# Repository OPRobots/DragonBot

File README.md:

# DragonBot
Robot siguelineas con succión centrifuga y STM32F1

## Hardware
- STM32F1 "BluePill"
- Driver de motores TB6612FNG
- 2x Motores Pololu N20 HP @3000rpm
- 1x Motor Brushless Rotorx
- LiPo 2S ~250 mAh
- 12x Sensores QRE1113
- 12x Potenciometros para regular la ganancia de los sensores
- Ruedas Scaleauto Procomp 1
- Chasis de PCB autosoportado con soportes de motores, ventilador y parachoques impresos en PLA

## Software
- Programado con VSCode y PlatformIO
- Funciones de PID y cálculo de posición en la línea
- Disponibles programas para configuración por defecto, coreless y brushless en diferentes ramas secundarias

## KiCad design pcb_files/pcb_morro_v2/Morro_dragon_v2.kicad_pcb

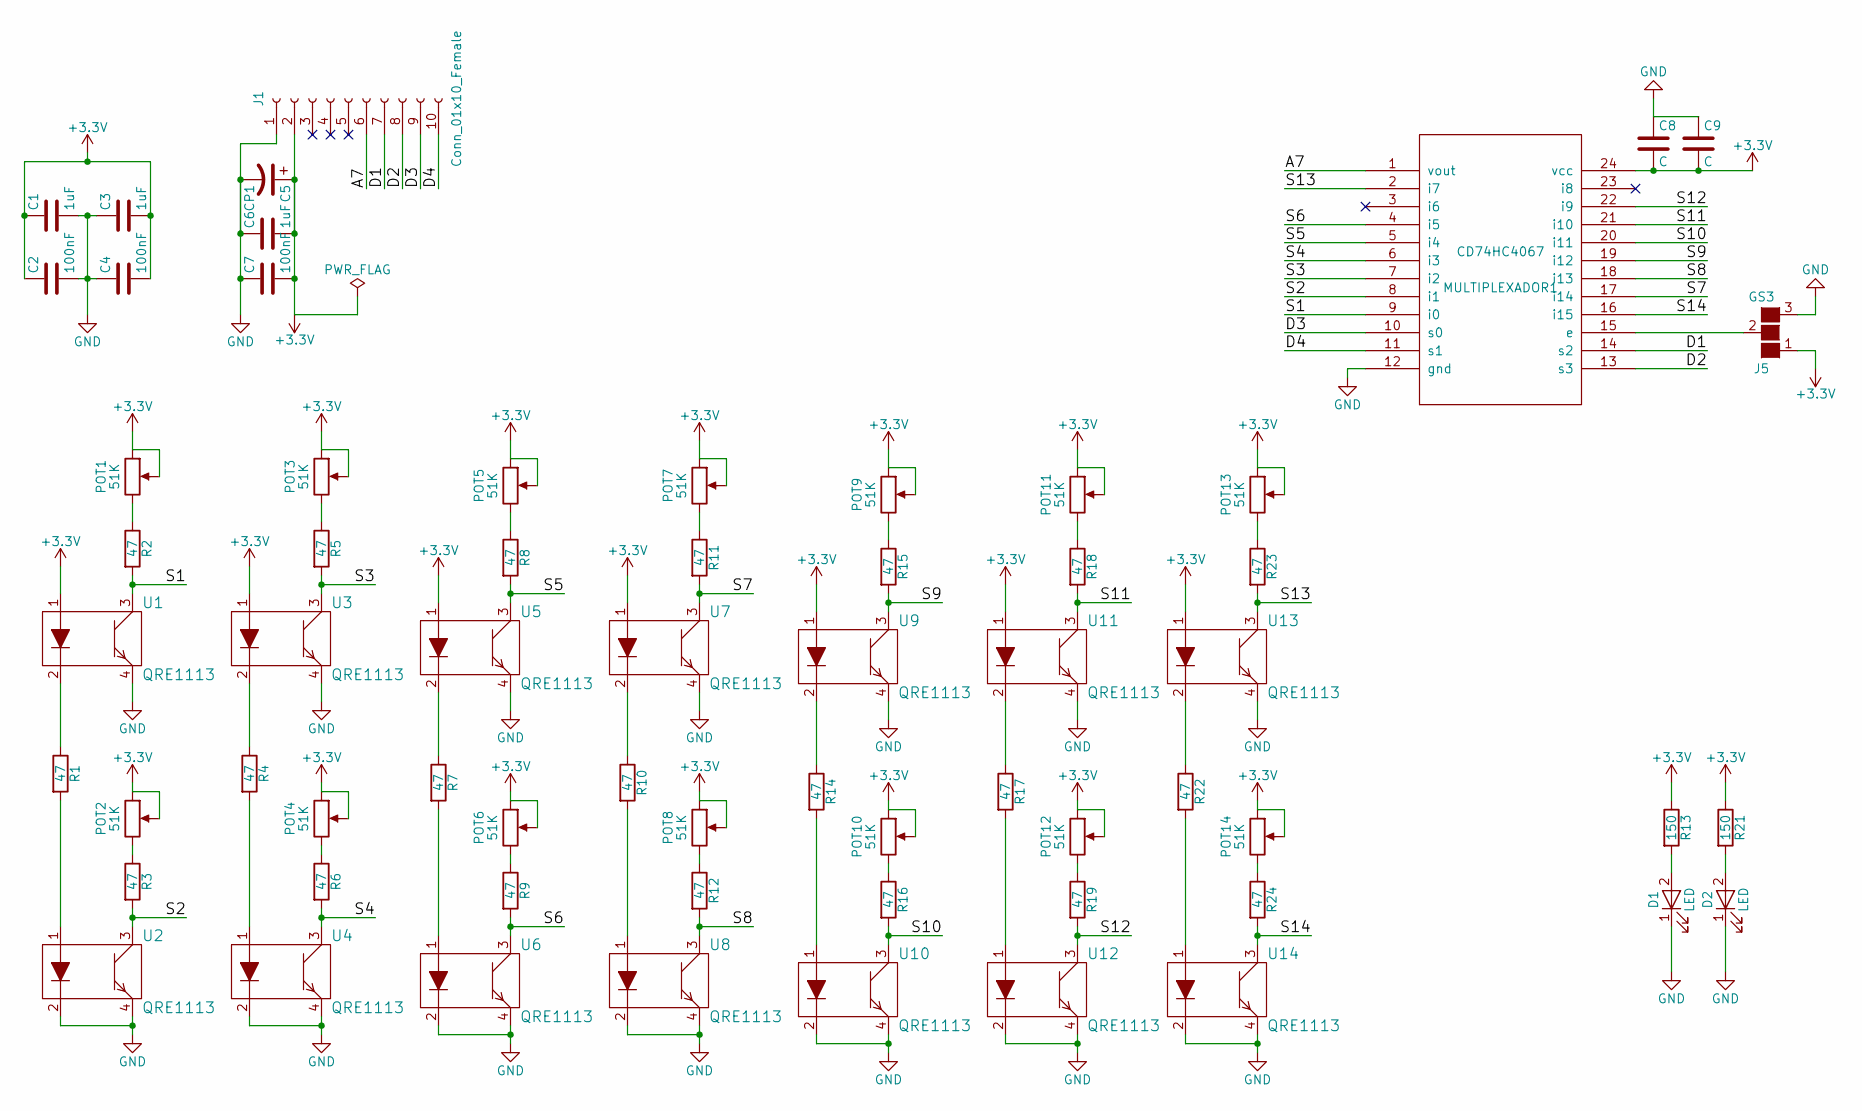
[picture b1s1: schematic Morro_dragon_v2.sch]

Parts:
C1, C3, C6: 1uF; C_0805
C2, C4, C7: 100nF; C_0805
C5: CP1; CP_Radial_D4.0mm_P1.50mm
C8, C9: C; C_0805
D1, D2: LED; LED_0805
J1: Conn_01x10_Female; Socket_Strip_Straight_1x10_Pitch1.27mm
J5: GS3
MULTIPLEXADOR1: CD74HC4067; TSSOP-24_4.4x7.8mm_Pitch0.65mm
POT1, POT2, POT3, POT4, POT5, POT6, POT7, POT8, POT9, POT10, POT11, POT12, POT13, POT14: 51K; Potentiometer_Trimmer-EVM3E
R1, R2, R3, R4, R5, R6, R7, R8, R9, R10, R11, R12, R14, R15, R16, R17, R18, R19, R22, R23, R24: 47; R_0805
R13, R21: 150; R_0805
U1, U2, U3, U4, U5, U6, U7, U8, U9, U10, U11, U12, U13, U14: QRE1113

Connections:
+3V3: C1.1, C2.1, C3.2, C4.2, C5.1, C6.2, C7.2, C8.2, C9.2, J1.2, J5.1 (G1), MULTIPLEXADOR1.24 (vcc), POT1.1, POT1.2, POT2.1, POT2.2, POT3.1, POT3.2, POT4.1, POT4.2, POT5.1, POT5.2, POT6.1, POT6.2, POT7.1, POT7.2, POT8.1, POT8.2, POT9.1, POT9.2, POT10.1, POT10.2, POT11.1, POT11.2, POT12.1, POT12.2, POT13.1, POT13.2, POT14.1, POT14.2, R13.1, R21.1, U1.1, U3.1, U5.1, U7.1, U9.1, U11.1, U13.1
/A7: J1.6, MULTIPLEXADOR1.1 (vout)
/D1: J1.7, MULTIPLEXADOR1.14 (s2)
/D2: J1.8, MULTIPLEXADOR1.13 (s3)
/D3: J1.9, MULTIPLEXADOR1.10 (s0)
/D4: J1.10, MULTIPLEXADOR1.11 (s1)
/S1: MULTIPLEXADOR1.9 (i0), R2.2, U1.3
/S2: MULTIPLEXADOR1.8 (i1), R3.2, U2.3
/S3: MULTIPLEXADOR1.7 (i2), R5.2, U3.3
/S4: MULTIPLEXADOR1.6 (i3), R6.2, U4.3
/S5: MULTIPLEXADOR1.5 (i4), R8.2, U5.3
/S6: MULTIPLEXADOR1.4 (i5), R9.2, U6.3
/S7: MULTIPLEXADOR1.17 (i14), R11.2, U7.3
/S8: MULTIPLEXADOR1.18 (i13), R12.2, U8.3
/S9: MULTIPLEXADOR1.19 (i12), R15.2, U9.3
/S10: MULTIPLEXADOR1.20 (i11), R16.2, U10.3
/S11: MULTIPLEXADOR1.21 (i10), R18.2, U11.3
/S12: MULTIPLEXADOR1.22 (i9), R19.2, U12.3
/S13: MULTIPLEXADOR1.2 (i7), R23.2, U13.3
/S14: MULTIPLEXADOR1.16 (i15), R24.2, U14.3
GND: C1.2, C2.2, C3.1, C4.1, C5.2, C6.1, C7.1, C8.1, C9.1, D1.1 (K), D2.1 (K), J1.1, J5.3 (G3), MULTIPLEXADOR1.12 (gnd), U1.4, U2.2, U2.4, U3.4, U4.2, U4.4, U5.4, U6.2, U6.4, U7.4, U8.2, U8.4, U9.4, U10.2, U10.4, U11.4, U12.2, U12.4, U13.4, U14.2, U14.4
unnamed: D1.2 (A), R13.2
unnamed: D2.2 (A), R21.2
unnamed: J5.2 (G2), MULTIPLEXADOR1.15 (e)
unnamed: POT1.3, R2.1
unnamed: POT2.3, R3.1
unnamed: POT3.3, R5.1
unnamed: POT4.3, R6.1
unnamed: POT5.3, R8.1
unnamed: POT6.3, R9.1
unnamed: POT7.3, R11.1
unnamed: POT8.3, R12.1
unnamed: POT9.3, R15.1
unnamed: POT10.3, R16.1
unnamed: POT11.3, R18.1
unnamed: POT12.3, R19.1
unnamed: POT13.3, R23.1
unnamed: POT14.3, R24.1
unnamed: R1.1, U1.2
unnamed: R1.2, U2.1
unnamed: R4.1, U3.2
unnamed: R4.2, U4.1
unnamed: R7.1, U5.2
unnamed: R7.2, U6.1
unnamed: R10.1, U7.2
unnamed: R10.2, U8.1
unnamed: R14.1, U9.2
unnamed: R14.2, U10.1
unnamed: R17.1, U11.2
unnamed: R17.2, U12.1
unnamed: R22.1, U13.2
unnamed: R22.2, U14.1

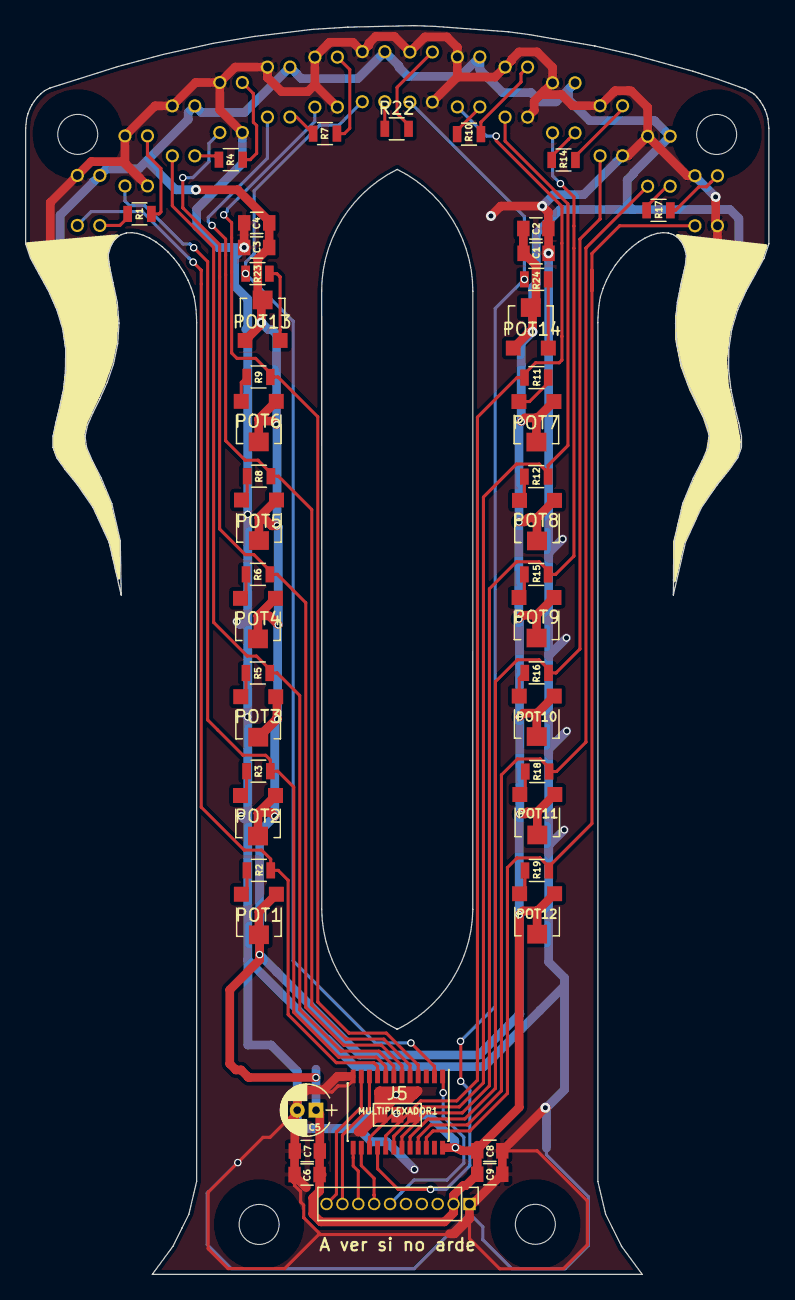
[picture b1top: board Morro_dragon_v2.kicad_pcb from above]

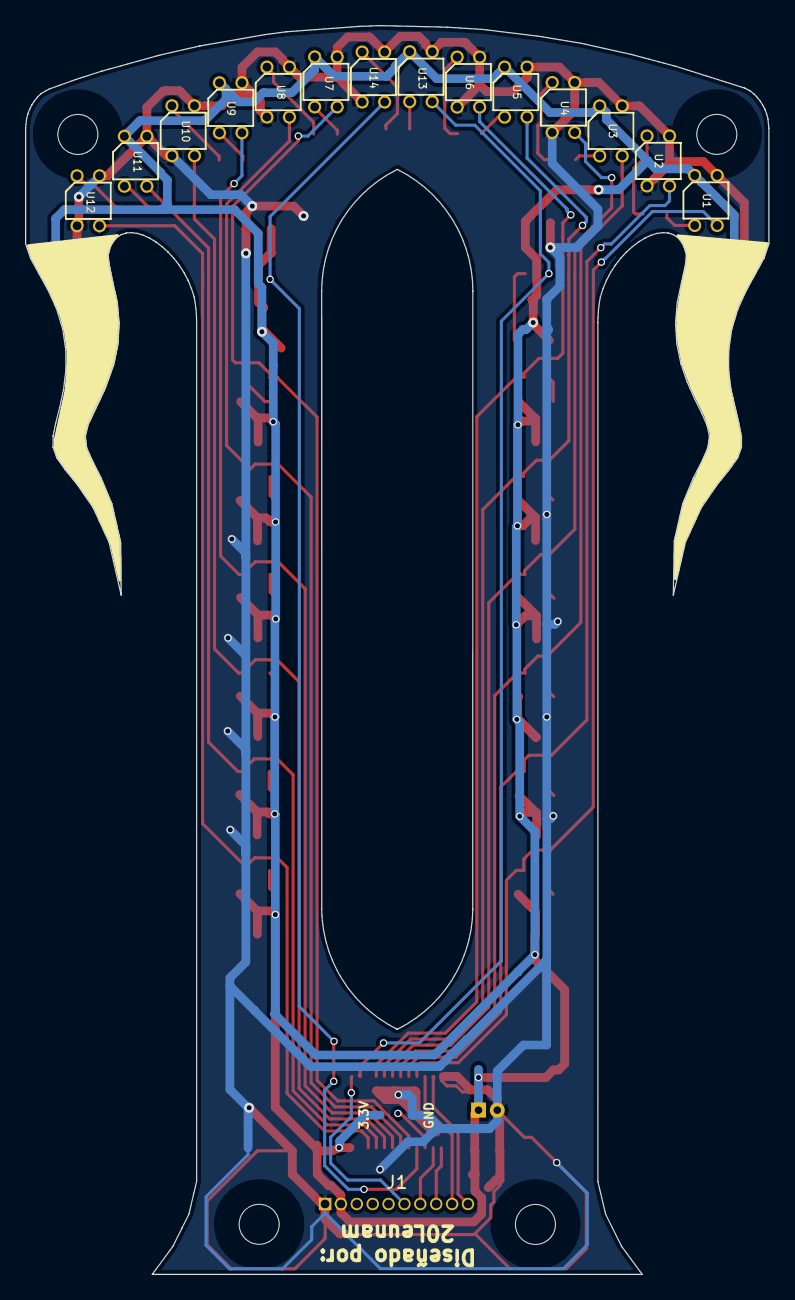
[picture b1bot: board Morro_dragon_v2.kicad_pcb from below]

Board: 2 copper layers, 59.4 x 99.9 mm, 65 parts (16 on the bottom side), 52 nets.

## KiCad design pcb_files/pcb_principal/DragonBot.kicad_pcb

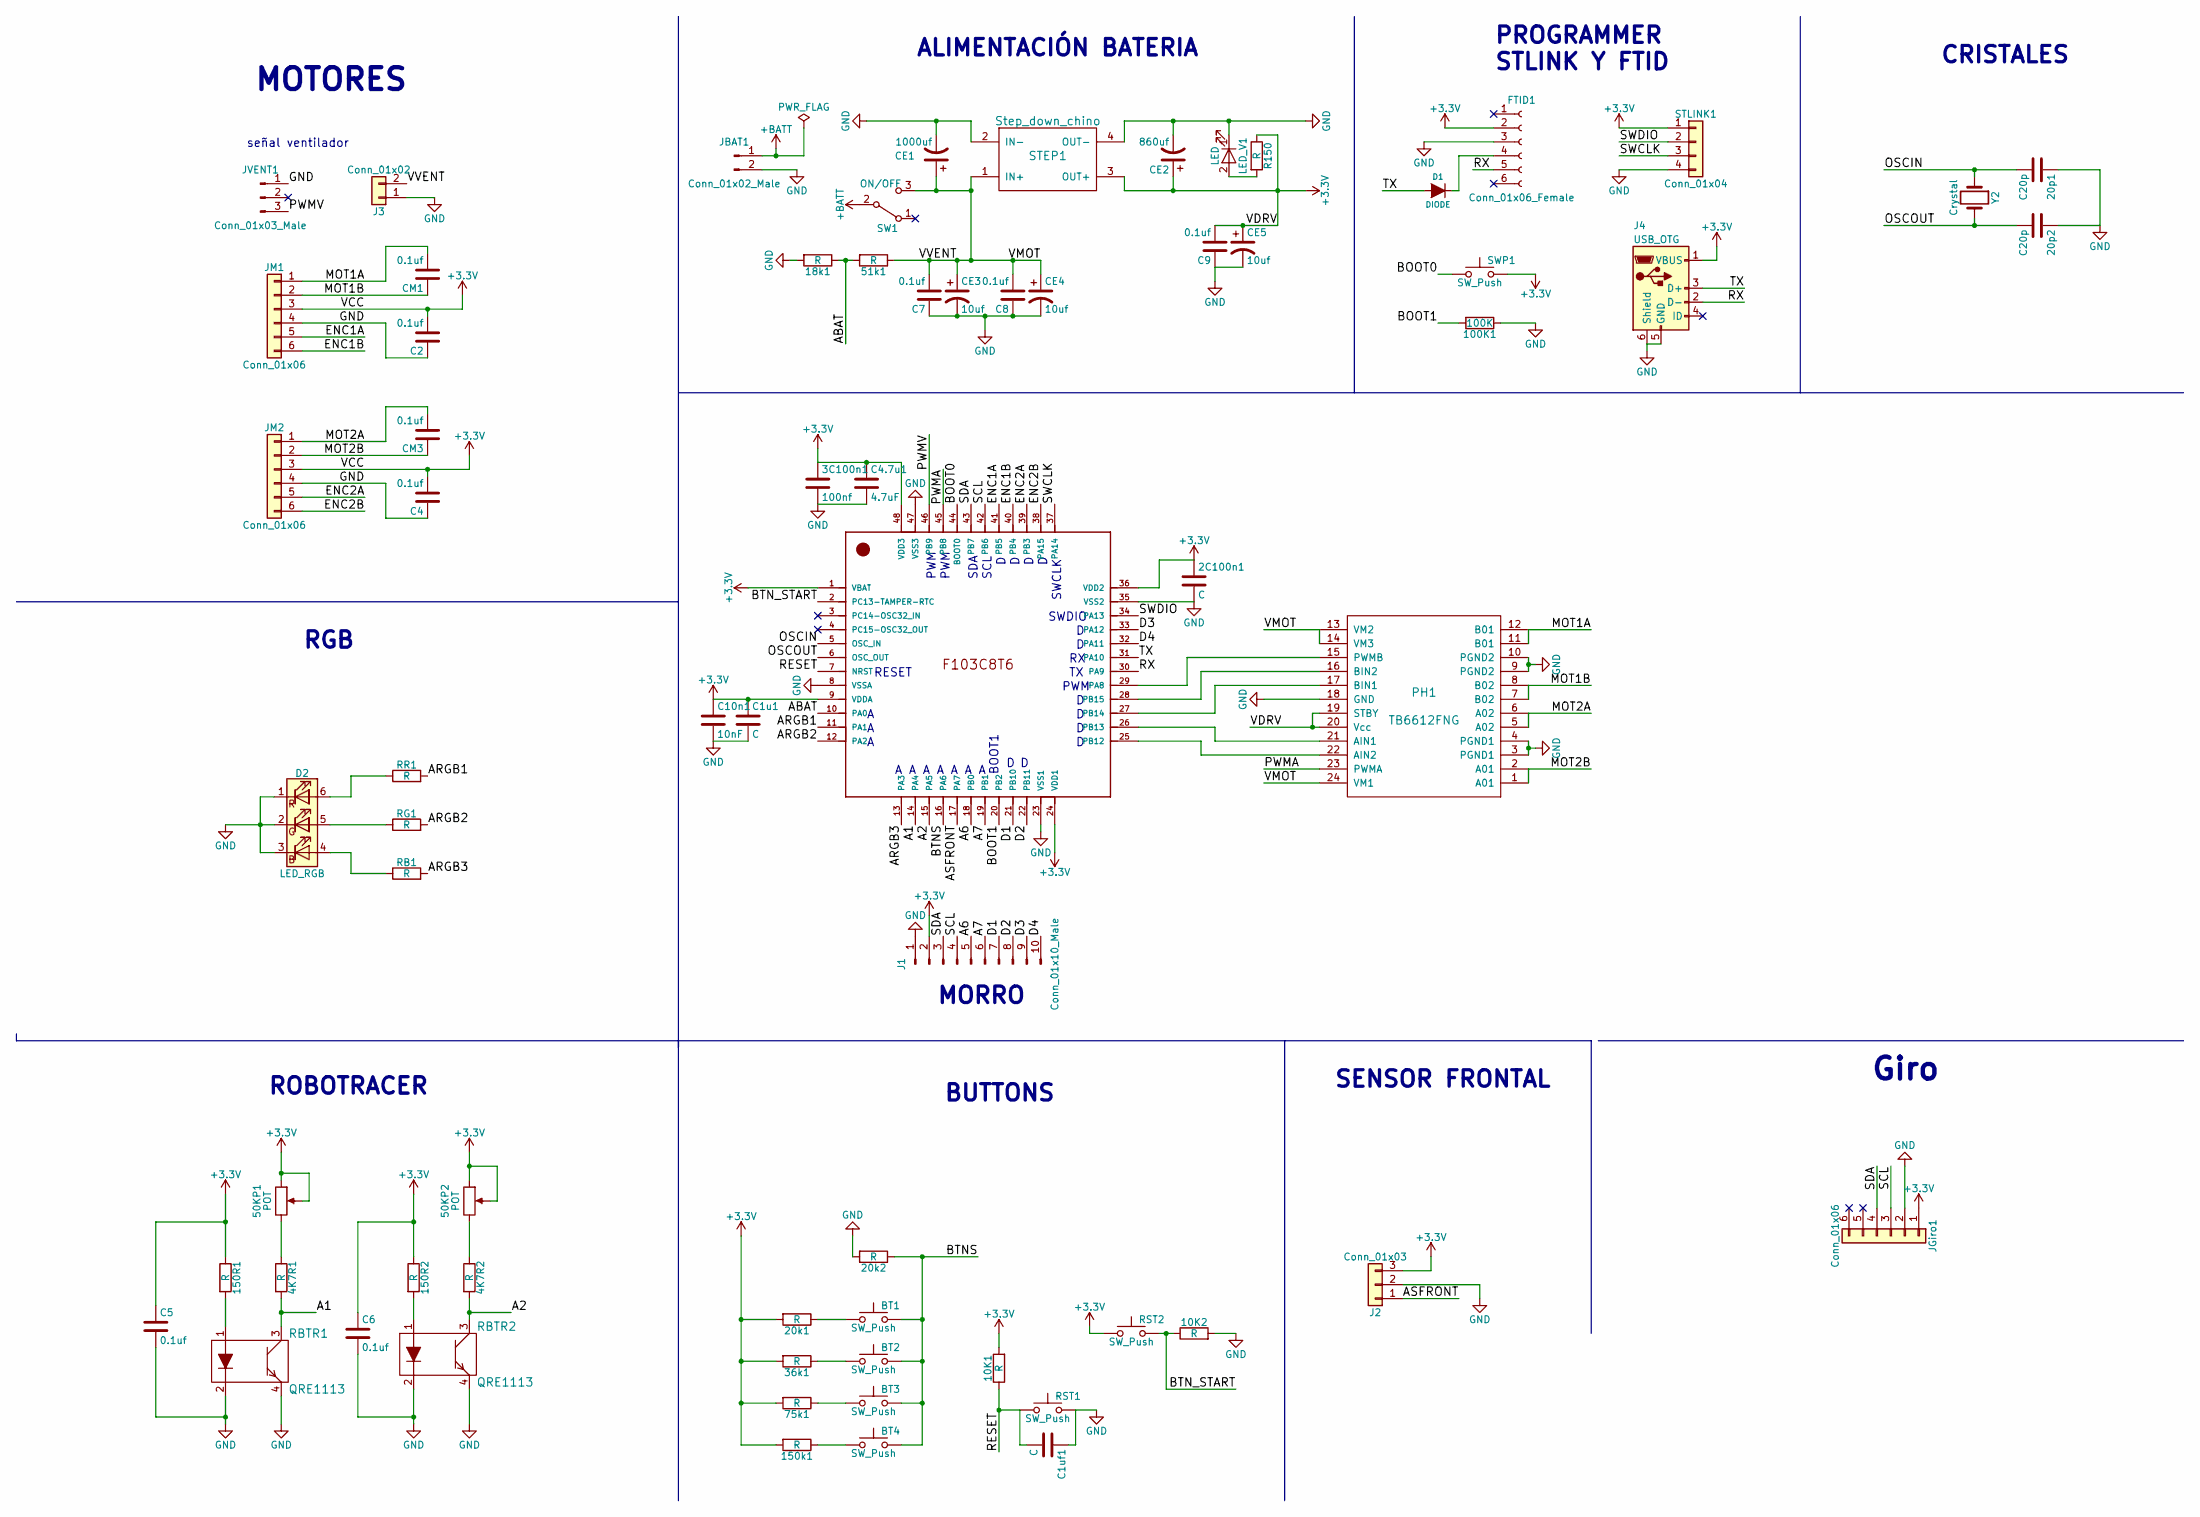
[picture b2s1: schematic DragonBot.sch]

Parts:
2C100n1: C; C_0805
3C100n1: 100nf; C_0805
4K7R1, 4K7R2, 10K1, 10K2, 18k1, 20k1, 20k2, 36k1, 51k1, 75k1, 150R1, 150R2, 150k1: R; R_0805
20p1, 20p2: C20p; C_0805
50KP1, 50KP2: POT; Potentiometer_Trimmer-EVM3E
100K1: 100K; R_0805
BT1, BT2, BT3, BT4: SW_Push; SW_DIP_x1_W8.61mm_Slide_LowProfile
C1u1, C1uf1: C; C_0805
C2, C4, C5, C6, C7, C8, C9: 0.1uf; C_0805
C4.7u1: 4.7uF; C_0805
C10n1: 10nF; C_0805
CE1: 1000uf; CP_Radial_D10.0mm_P7.50mm
CE2: 860uf; CP_Radial_D8.0mm_P5.00mm
CE3, CE4, CE5: 10uf; CP_Radial_D4.0mm_P2.00mm
CM1, CM3: 0.1uf; C_Disc_D3.4mm_W2.1mm_P2.50mm
D1: DIODE; D_A-405_P7.62mm_Horizontal
D2: LED_RGB; LED_RGB_5050-6
FTID1: Conn_01x06_Female; Socket_Strip_Straight_1x06_Pitch2.54mm
J1: Conn_01x10_Male; Pin_Header_Angled_1x10_Pitch1.27mm
J2: Conn_01x03; Pin_Header_Straight_1x03_Pitch2.54mm
J3: Conn_01x02; Pin_Header_Straight_1x02_Pitch2.54mm
J4: USB_OTG; USB_Mini-B
JBAT1: Conn_01x02_Male; Pin_Header_Straight_1x02_Pitch2.54mm
JGiro1: Conn_01x06; Pin_Header_Straight_1x06_Pitch2.54mm
JM1, JM2: Conn_01x06; Pin_Header_Straight_1x06_Pitch2.54mm
JVENT1: Conn_01x03_Male; Pin_Header_Straight_1x03_Pitch2.54mm
LED_V1: LED; LED_0805_HandSoldering
PH1: TB6612FNG; SSOP-24_5.3x8.2mm_Pitch0.65mm
R150: R; R_0805
RB1: R; R_0805
RBTR1, RBTR2: QRE1113
RG1: R; R_0805
RR1: R; R_0805
RST1, RST2: SW_Push; SW_DIP_x1_W8.61mm_Slide_LowProfile
STEP1: Step_down_chino
STLINK1: Conn_01x04; Pin_Header_Straight_1x04_Pitch2.54mm
SW1: ON/OFF; Pin_Header_Straight_1x03_Pitch2.54mm
SWP1: SW_Push; SW_DIP_x1_W8.61mm_Slide_LowProfile
U1: STM32F103C8T6; LQFP-48_7x7mm_Pitch0.5mm; Digi-Key_Part_Number 497-6063-ND
Y2: Crystal; Crystal_HC50_Vertical

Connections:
+3V3: 2C100n1.1, 3C100n1.1, 10K1.2, 20k1.2, 36k1.2, 50KP1.1, 50KP1.2, 50KP2.1, 50KP2.2, 75k1.2, 150R1.1, 150R2.1, 150k1.2, C1u1.1, C2.2, C4.2, C4.7u1.1, C5.1, C6.1, C9.2, C10n1.1, CE2.1, CE5.1, FTID1.2, J1.2, J2.3, J4.1 (VBUS), JGiro1.1, JM1.3, JM2.3, PH1.19 (STBY), PH1.20 (Vcc), R150.1, RST2.1, STEP1.3 (OUT+), STLINK1.1, SWP1.2, U1.1 (VBAT), U1.9 (VDDA), U1.24 (VDD1), U1.36 (VDD2), U1.48 (VDD3)
+BATT: JBAT1.1, SW1.2 (B)
/A1: 4K7R1.2, RBTR1.3, U1.14 (PA4)
/A2: 4K7R2.2, RBTR2.3, U1.15 (PA5)
/A6: J1.5, U1.18 (PB0)
/A7: J1.6, U1.19 (PB1)
/ABAT: 18k1.1, 51k1.2, U1.10 (PA0)
/ARGB1: RR1.2, U1.11 (PA1)
/ARGB2: RG1.2, U1.12 (PA2)
/ARGB3: RB1.2, U1.13 (PA3)
/ASFRONT: J2.1, U1.17 (PA7)
/BOOT0: SWP1.1, U1.44 (BOOT0)
/BOOT1: 100K1.2, U1.20 (PB2)
/BTNS: 20k2.1, BT1.2, BT2.2, BT3.2, BT4.2, U1.16 (PA6)
/BTN_START: 10K2.1, RST2.2, U1.2 (PC13-TAMPER-RTC)
/D1: J1.7, U1.21 (PB10)
/D2: J1.8, U1.22 (PB11)
/D3: J1.9, U1.33 (PA12)
/D4: J1.10, U1.32 (PA11)
/ENC1A: JM1.5, U1.41 (PB5)
/ENC1B: JM1.6, U1.40 (PB4)
/ENC2A: JM2.5, U1.39 (PB3)
/ENC2B: JM2.6, U1.38 (PA15)
/MOT1A: CM1.2, JM1.1, PH1.11 (B01), PH1.12 (B01)
/MOT1B: CM1.1, JM1.2, PH1.7 (B02), PH1.8 (B02)
/MOT2A: CM3.2, JM2.1, PH1.5 (A02), PH1.6 (A02)
/MOT2B: CM3.1, JM2.2, PH1.1 (A01), PH1.2 (A01)
/OSCIN: 20p1.2, U1.5 (OSC_IN), Y2.1
/OSCOUT: 20p2.2, U1.6 (OSC_OUT), Y2.2
/PWMA: PH1.23 (PWMA), U1.45 (PB8)
/PWMV: JVENT1.3, U1.46 (PB9)
/RESET: 10K1.1, C1uf1.2, RST1.1, U1.7 (NRST)
/RX: FTID1.5, J4.2 (D-), U1.30 (PA9)
/SCL: J1.4, JGiro1.3, U1.42 (PB6)
/SDA: J1.3, JGiro1.4, U1.43 (PB7)
/SWCLK: STLINK1.3, U1.37 (PA14)
/SWDIO: STLINK1.2, U1.34 (PA13)
/TX: D1.1 (A), J4.3 (D+), U1.31 (PA10)
/VMOT: 51k1.1, C7.2, C8.2, CE1.1, CE3.1, CE4.1, J3.2, PH1.13 (VM2), PH1.14 (VM3), PH1.24 (VM1), STEP1.1 (IN+), SW1.3 (C)
GND: 2C100n1.2, 3C100n1.2, 10K2.2, 18k1.2, 20k2.2, 20p1.1, 20p2.1, 100K1.1, C1u1.2, C1uf1.1, C2.1, C4.1, C4.7u1.2, C5.2, C6.2, C7.1, C8.1, C9.1, C10n1.2, CE1.2, CE2.2, CE3.2, CE4.2, CE5.2, D2.1 (RK), D2.2 (GK), D2.3 (BK), FTID1.3, J1.1, J2.2, J3.1, J4.5 (GND), J4.6 (Shield), JBAT1.2, JGiro1.2, JM1.4, JM2.4, JVENT1.1, LED_V1.1 (K), PH1.3 (PGND1), PH1.4 (PGND1), PH1.9 (PGND2), PH1.10 (PGND2), PH1.18 (GND), RBTR1.2, RBTR1.4, RBTR2.2, RBTR2.4, RST1.2, STEP1.2 (IN-), STEP1.4 (OUT-), STLINK1.4, U1.8 (VSSA), U1.23 (VSS1), U1.35 (VSS2), U1.47 (VSS3)
unnamed: 4K7R1.1, 50KP1.3
unnamed: 4K7R2.1, 50KP2.3
unnamed: 20k1.1, BT1.1
unnamed: 36k1.1, BT2.1
unnamed: 75k1.1, BT3.1
unnamed: 150R1.2, RBTR1.1
unnamed: 150R2.2, RBTR2.1
unnamed: 150k1.1, BT4.1
unnamed: D1.2 (K), FTID1.4
unnamed: D2.4 (BA), RB1.1
unnamed: D2.5 (GA), RG1.1
unnamed: D2.6 (RA), RR1.1
unnamed: LED_V1.2 (A), R150.2
unnamed: PH1.15 (PWMB), U1.29 (PA8)
unnamed: PH1.16 (BIN2), U1.28 (PB15)
unnamed: PH1.17 (BIN1), U1.27 (PB14)
unnamed: PH1.21 (AIN1), U1.26 (PB13)
unnamed: PH1.22 (AIN2), U1.25 (PB12)

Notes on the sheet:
RGB
ROBOTRACER
BUTTONS
MORRO
PROGRAMMER STLINK Y FTID
MOTORES
ALIMENTACIÓN BATERIA
CRISTALES
señal ventilador
SENSOR FRONTAL
SWDIO
RESET
BOOT1
PWM
SDA
SCL
SWCLK
Giro

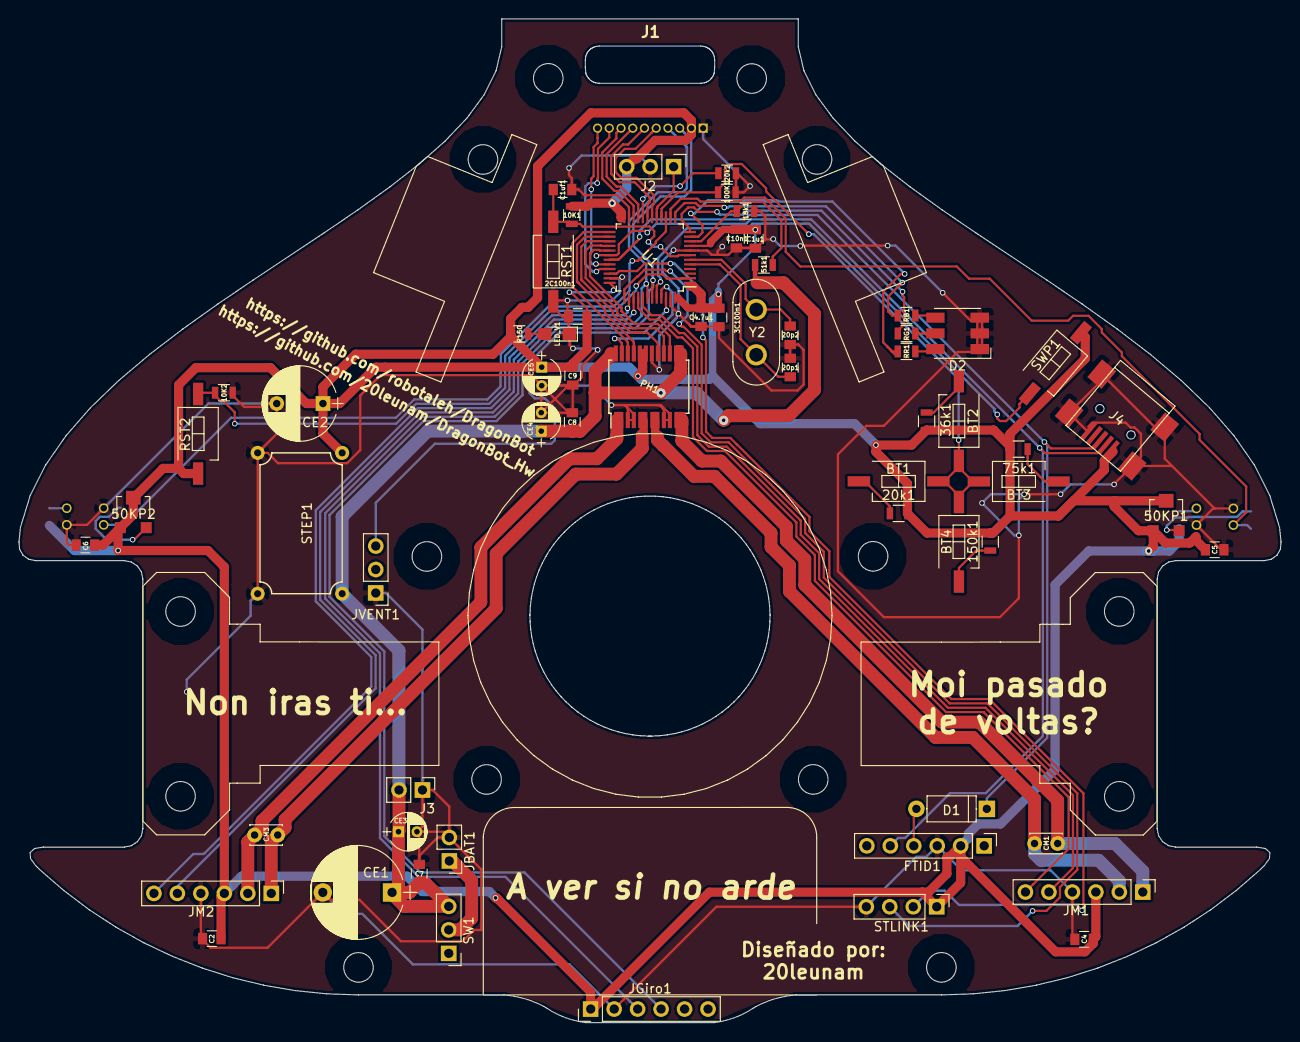
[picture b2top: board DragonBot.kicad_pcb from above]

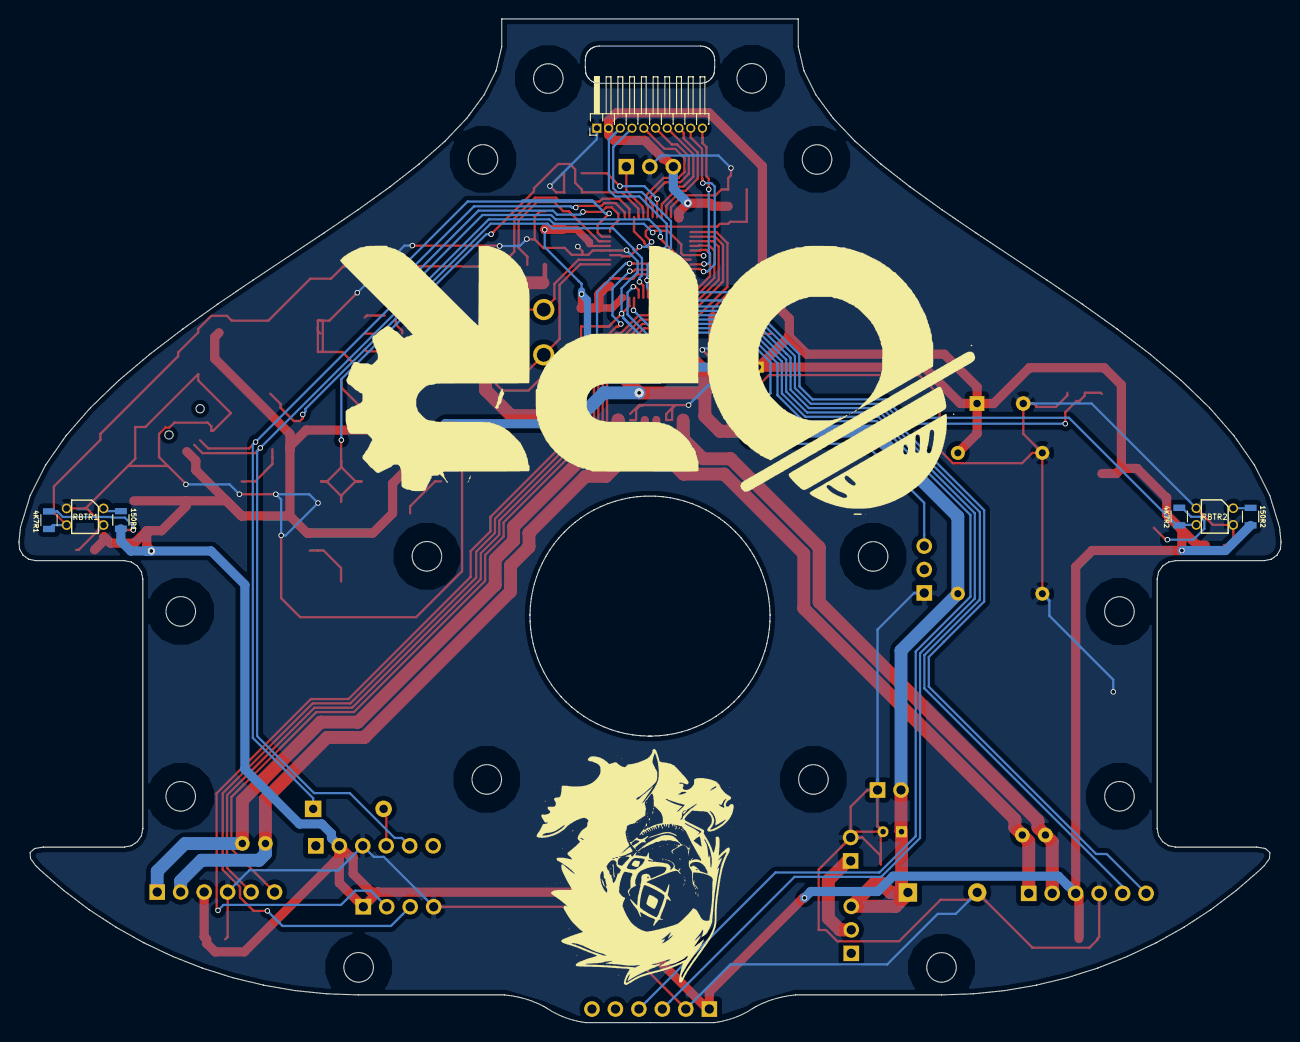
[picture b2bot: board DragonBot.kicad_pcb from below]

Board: 2 copper layers, 136.6 x 108.6 mm, 70 parts (7 on the bottom side), 58 nets.

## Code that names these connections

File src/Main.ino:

//////////////////////////
// INCLUDE de LIBRERIAS //
//////////////////////////
/**
 * Calibración del PID desde la APP android PIDfromBT
 * https://github.com/robotaleh/PIDfromBT
 */
#include <Filter.h>
#include <MegunoLink.h>
#include <PIDfromBT.h>

////////////////////////
// SELECTOR DE ROBOT  //
////////////////////////
// #define DRAGON_A 1
#define DRAGON_B 1

// #define MORRO_ANCHO 1
#define MORRO_ESTRECHO 1

////////////
// MODOS  //
////////////
#define MODO_LINEA 1

#define LINEA_NEGRA 1
#define LINEA_BLANCA 2

#define LIPO_2S 1
#define LIPO_3S 2

#define MODO_MS 1
#define MODO_PWM 2

///////////////////
// CONFIGURACION //
///////////////////
#define MILLIS_INICIO 5000
#define PISTA MODO_LINEA
#define LINEA LINEA_NEGRA
#define LIPO LIPO_2S
#define VELOCIDAD MODO_PWM
#define TIEMPO_CALIBRADO 2500
#define CALIBRAR_SENSORES true

//////////////
// SENSORES //
//////////////
#define TIEMPO_SIN_PISTA 200

#ifdef MORRO_ANCHO
#define NUMERO_SENSORES 12
#define SENSOR_1 0
#define SENSOR_2 1
#define SENSOR_3 2
#define SENSOR_4 3
#define SENSOR_5 4
#define SENSOR_6 5
#define SENSOR_7 14
#define SENSOR_8 13
#define SENSOR_9 12
#define SENSOR_10 11
#define SENSOR_11 10
#define SENSOR_12 9

#elif MORRO_ESTRECHO
#define NUMERO_SENSORES 14
#define SENSOR_1 0
#define SENSOR_2 1
#define SENSOR_3 2
#define SENSOR_4 3
#define SENSOR_5 4
#define SENSOR_6 5
#define SENSOR_7 7
#define SENSOR_8 15
#define SENSOR_9 14
#define SENSOR_10 13
#define SENSOR_11 12
#define SENSOR_12 11
#define SENSOR_13 10
#define SENSOR_14 9
#endif
#define SENSOR_ROBOTRACER_DERECHO PA4
#define SENSOR_ROBOTRACER_IZQUIERDO PA5

#define LECTURA_MAXIMO_SENSORES_LINEA 4096
#define LECTURA_MINIMO_SENSORES_LINEA 0
#define CALIBRADO_MAXIMO_SENSORES_LINEA 2000
#define CALIBRADO_MINIMO_SENSORES_LINEA 0

///////////////////
// MULTIPLEXADOR //
///////////////////
#define MUX_LECTURA PB1
#define MUX_CANAL_0 PA12
#define MUX_CANAL_1 PA11
#define MUX_CANAL_2 PB10
#define MUX_CANAL_3 PB11

/////////////
// MOTORES //
/////////////
#ifdef DRAGON_A
#define MOTOR_DERECHO_ADELANTE PB15
#define MOTOR_DERECHO_ATRAS PB14
#define MOTOR_IZQUIERDO_ADELANTE PB12
#define MOTOR_IZQUIERDO_ATRAS PB13
#endif

#ifdef DRAGON_B
#define MOTOR_DERECHO_ADELANTE PB14
#define MOTOR_DERECHO_ATRAS PB15
#define MOTOR_IZQUIERDO_ADELANTE PB12
#define MOTOR_IZQUIERDO_ATRAS PB13
#endif

#define MOTOR_DERECHO_PWM PA8
#define MOTOR_IZQUIERDO_PWM PB8
#define MOTOR_SUCCION PB9

//////////////
// ENCODERS //
//////////////
#define MOTOR_DERECHO_ENCODER_A PB5
#define MOTOR_DERECHO_ENCODER_B PB4
#define MOTOR_IZQUIERDO_ENCODER_A PA15
#define MOTOR_IZQUIERDO_ENCODER_B PB3

//////////
// LEDS //
//////////
#define RED_RGB_R PA1
#define RED_RGB_G PA2
#define RED_RGB_B PA3

///////////////////////////////////
// VARIABLES DE CONTROL DE LEDS  //
///////////////////////////////////
int colorRGB[] = {255, 0, 0};
int colorDesc = 0;
int colorAsc = 1;
long ultimoCambioRGB = 0;

/////////////
// BOTONES //
/////////////
#define BTN PC13
#define BTN_CRUCETA PA6

//////////
// MISC //
//////////
#define NIVEL_BATERIA PA0

///////////////
// VARIABLES //
///////////////
float anguloGiro = 0;
float anguloGiroR = 0;
float velocidadW = 0;
float velocidadMs = 0;
float posXm = 0;
float posYm = 0;
int velocidad = 0;
float velocidadMsIdeal = 0;
float velocidadMsIdealBase = 0;
int velocidadPercentBase = 0;
int velocidadSuccion = 0;
int velocidadSuccionBase = 50;
int velocidadMaxima = 255;
long ultimaLinea = 0;
long ultimaBateria = 0;
bool avisoBateria = false;
int intervaloAvisoBateria = 500;
long millisInitESC = -1;
bool ESCIniciado = false;

//////////////////////////
// VARIABLES DE CONTROL //
//////////////////////////
int posicionActual = 0;
int posicionIdeal = 0;
int posicionIdealObjetivo;
float errorAnterior = 0;
float integralErrores = 0;
float kp;
float ki;
float kd;
float kpVelocidad = 5;
float kdVelocidad = 10;
float ultimoErrorVelocidad = 0;
int correccion = 0;

////////////////////////////
// VARIABLES DE ENCODERS  //
////////////////////////////
#define ENCODER_PPR 119
#define RUEDAS_RADIO 0.01275
float ticksMm = 1.444f;
long ticksDerechoAnteriores = 0;
long ticksIzquierdoAnteriores = 0;
volatile long ticksDerecho = 0;
volatile long ticksIzquierdo = 0;

///////////////////////////
// VARIABLES DE SENSORES //
///////////////////////////
#ifdef MORRO_ANCHO
int pinesSensores[] = {SENSOR_1, SENSOR_2, SENSOR_3, SENSOR_4, SENSOR_5, SENSOR_6, SENSOR_7, SENSOR_8, SENSOR_9, SENSOR_10, SENSOR_11, SENSOR_12};
int valoresSensores[] = {0, 0, 0, 0, 0, 0, 0, 0, 0, 0, 0, 0};
int valoresSensoresRaw[] = {0, 0, 0, 0, 0, 0, 0, 0, 0, 0, 0, 0};
#elif MORRO_ESTRECHO
int pinesSensores[] = {SENSOR_1, SENSOR_2, SENSOR_3, SENSOR_4, SENSOR_5, SENSOR_6, SENSOR_7, SENSOR_8, SENSOR_9, SENSOR_10, SENSOR_11, SENSOR_12, SENSOR_13, SENSOR_14};
int valoresSensores[] = {0, 0, 0, 0, 0, 0, 0, 0, 0, 0, 0, 0, 0, 0};
int valoresSensoresRaw[] = {0, 0, 0, 0, 0, 0, 0, 0, 0, 0, 0, 0, 0, 0};
#endif

///////////////////////////////
// VARIABLES DE CALIBRACIÓN  //
///////////////////////////////
#ifdef MORRO_ANCHO
int valoresCalibracionMinimos[] = {4096, 4096, 4096, 4096, 4096, 4096, 4096, 4096, 4096, 4096, 4096, 4096};
int valoresCalibracionMaximos[] = {0, 0, 0, 0, 0, 0, 0, 0, 0, 0, 0, 0};
#elif MORRO_ESTRECHO
int valoresCalibracionMinimos[] = {4096, 4096, 4096, 4096, 4096, 4096, 4096, 4096, 4096, 4096, 4096, 4096, 4096, 4096};
int valoresCalibracionMaximos[] = {0, 0, 0, 0, 0, 0, 0, 0, 0, 0, 0, 0, 0, 0};
#endif
int umbralesCalibracionSensores[NUMERO_SENSORES];
int valorCalibradoMaximo;
int valorCalibradoMinimo;
int posicionMaxima;
int posicionMinima;

///////////////////////////////
// VARIABLES DE COMPETICIÓN  //
///////////////////////////////
bool competicionIniciada = false;

/////////////////////////////////////////
// VARIABLES DE MENÚ DE CONFIGURACIÓN  //
/////////////////////////////////////////
#define NUMERO_COMBINACIONES 10
#define CRUCETA_ARRIBA 1460
#define CRUCETA_ABAJO 475
#define CRUCETA_DERECHA 860
#define CRUCETA_IZQUIERDA 2040
#define CRUCETA_ARRIBA_ABAJO 1670
#define CRUCETA_DERECHA_IZQUIERDA 2280
#define CRUCETA_ARRIBA_DERECHA 1840
#define CRUCETA_DERECHA_ABAJO 1160
#define CRUCETA_ABAJO_IZQUIERDA 2170
#define CRUCETA_IZQUIERDA_ARRIBA 2490
int crucetaCombinaciones[] = {CRUCETA_ARRIBA,
                              CRUCETA_ABAJO,
                              CRUCETA_DERECHA,
                              CRUCETA_IZQUIERDA,
                              CRUCETA_ARRIBA_ABAJO,
                              CRUCETA_DERECHA_IZQUIERDA,
                              CRUCETA_ARRIBA_DERECHA,
                              CRUCETA_DERECHA_ABAJO,
                              CRUCETA_ABAJO_IZQUIERDA,
                              CRUCETA_IZQUIERDA_ARRIBA};
#define NUMERO_VELOCIDADES 10
int velocidad_menu = 0;
#define NUMERO_VELOCIDADES_SUCCION 9
int velocidad_succion_menu = 0;

//////////////////////////////
// INICIALIZACION LIBRERIAS //
//////////////////////////////
HardwareTimer TimerPID(2);
bool timerPID_pause = false;
HardwareTimer TimerBrushless(3);
PIDfromBT CalibracionPID(&kp, &ki, &kd, &velocidad, &posicionIdeal, &velocidadSuccion, DEBUG);
ExponentialFilter<long> filtroBateria(15, 0);

void setup() {
  inicia_todo();
  inicia_timer_Brushless();
  nivel_bateria(false);
  calibra_sensores();
  delay(100);
}

void loop() {
  // CalibracionPID.update();
  if (!competicionIniciada) {
    btn_cruceta();
    if (!btn_pulsado()) {
      delay(100);
      if (btn_pulsado()) {
        set_color_RGB(255, 0, 0);
        while (btn_pulsado()) {
        }
        long millisIniciales = millis();
        int tiempoPasado = 5;
        while (millis() < (millisIniciales + MILLIS_INICIO)) {
          tiempoPasado = millis() - millisIniciales;
          byte r = 0, g = 0;
          r = map(tiempoPasado, 0, MILLIS_INICIO, 255, 0);
          g = map(tiempoPasado, 0, 1000, 0, 255);
          set_color_RGB(r, g, 0);
          if ((tiempoPasado > MILLIS_INICIO * 0.75f || MILLIS_INICIO == 0) && velocidadSuccion == 0 && velocidadSuccionBase > 0) {
            velocidadSuccion = 50;
          }
        }
        ticksDerecho = 0;
        ticksIzquierdo = 0;
        ticksDerechoAnteriores = 0;
        ticksIzquierdoAnteriores = 0;
        velocidadMs = 0;
        ultimaLinea = millis();
        inicia_timer_PID();
        competicionIniciada = true;
        set_color_RGB(0, 0, 0);
        if (VELOCIDAD == MODO_MS) {
          velocidadMsIdeal = velocidadMsIdealBase;
        } else {
          velocidad = map(velocidadPercentBase, 0, 100, 0, 255);
        }
        velocidadSuccion = velocidadSuccionBase;
      }
    }
  }
}

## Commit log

2017-09-28 Ficheros iniciales del proyecto PIO
2017-09-30 Añadir pines iniciales
2017-10-01 Añade fichero Init.ino
2017-10-01 Añade funciones iniciales de inicialización.
2017-10-01 Añade inicialización de motores.
2017-10-01 Añade librería I2C; Wire
2017-10-01 Añade librería sensores láser; VL53L0X
2017-10-01 Añade inicialización de sensores láser VL53L0X
2017-10-01 Añade inicialización de sensores QRE1113
2017-10-01 Añade inicialización de LED, BTN y SWITCH.
2017-10-01 Añade inicialización del puerto Serial.
2017-10-02 Establece protocolo de subida
2017-10-02 Fix inicialización de Puerto Serial
2017-10-08 Añade configuración inicial de circuito.
2017-10-08 Añade fichero para lecturas de sensores
2017-10-08 Añade funciones base de lectura de sensores
2017-10-08 Añade funciones principales de calibrado de sensores de línea
2017-10-08 Añade lectura escalada de sensores
2017-10-29 Corrige error en calibrado de sensores de línea.
2017-10-29 Añade cálculo de posición para circuitos de línea.
2017-11-07 Añade librería PIDfromBT para calibración de PID a distancia.
2017-11-07 Corrige pines de los motores
2017-11-07 Establece umbrales para límite de blanco-negro de los sensores de línea
2017-11-07 Añade fichero de movimientos
2017-11-07 Añade función para cálculo de la posición del robot sobre la línea.
2017-11-12 Añade uso de los encoders
2017-11-12 Añade función de cálculo de la corrección mediante PID
2017-11-12 Añade función para calcular y asignar aceleraciones
2017-11-12 Añade función de manejo de velocidades de los motores.
2017-11-12 Añade comprobaciones de parada de emergencia, en caso de perder la línea
2017-11-12 Añade mecanismo de arranque y configuraciones iniciales de competición.
2017-11-14 Añade librería de filtrado MLP Filter.h
2017-11-14 Modifica la asignación de velocidades para evitar marcha atrás.
2017-11-17 Corrige pines de sensores láser
2017-11-17 Añade lectura de sensores láser.
2017-11-17 Corrige lectura escalada de sensores de línea.
2017-11-17 Añade pausa al hacer doble calibración.
2017-11-17 Reduce el rango de mapeo a 4000
2017-11-17 Mejora la calibración y cálculo de medias
2017-11-17 Actualiza comentario de mapeo de sensores.
2017-11-17 Añade cálculo de posición en degradados.
2017-11-17 Cambia el modo a Degradado
2017-11-17 Actualiza los valores de saturación de sensores.
2017-11-18 Añade funcion para saber si un sensor está dentro del degradado.
2017-11-18 Añade check de sensores en degradado para mantener posición al perderlo
2017-11-18 Añade librería ATDelay para controlar ejecuciones periodicas facilmente.
2017-11-18 Indenta el fichero correctamente.
2017-11-18 Añade función para realuzar un cambio ideal progresivo.
2017-11-18 Añade un filtrado para suavizar los cambios en el ideal.
2017-11-18 Fuerza el apagado de led para cuando no se realiza calibración.
2017-11-19 Baja los timeout de los sensores láser e inicia el frontal como continuo
2017-11-19 Actualiza la función de lectura de sensores láser.
2017-11-19 Establece el ideal inicial como la posición en la que inicia.
2017-11-19 Indenta comentarios
2017-11-19 Añade ATDelay para controlar el tiempo entre cada lectura frontal
2017-11-19 Añade variable sin uso para evitar cambios de ideal desde la APP de PID
2017-11-19 Elimina los filtros de los sensores láser
2017-11-19 Añade variables para cambio progresivo de ideal
2017-11-19 Ajusta los filtros de posición y cambio de ideal
2017-11-19 Añade uso de función de comprobación de sensores láser.
2017-11-19 Añade llamada a función de cambio progresivo de ideal.
2017-11-19 Añade función de pruebas de detección frontal
2017-11-19 Añade apagado de led al finalizar cambio de ideal.
2017-11-19 Cambia orden de reseteo de ATDelay
2017-11-19 Elimina código sin usar
2017-11-19 Aumenta tiempo entre lecturas frontales
2017-11-22 Mejora lógica de cambio de lado, permitiendo cambiar solo en rectas.
2017-11-22 Añade nomenclatura para los sensores láser
2018-03-13 Rollback a estado inicial.
2018-03-13 Añade variables y defines iniciales
2018-03-13 Elimina librería LIDAR
2018-03-13 Actualiza librería PIDfromBT
2018-03-13 Añade la librería de calibración del PID
2018-03-13 Añade inicialización de todos los componentes
2018-03-13 Añade modos de pista y configuraciones
2018-03-13 Apaga el RGB al iniciarlo
2018-03-13 Añade funciones básicas para control de leds (RGB)
2018-03-13 Añade funciones principales de lectura de sensores de pista
2018-03-13 Añade funciones principales para el calibrado de los sensores de pista
2018-03-13 Añade funciones básicas de control: Cálculo posición, PID y Velocidades
2018-03-13 Corrige lecturas mapeadas de los sensores de pista
2018-03-15 Añade pin de chopeo de sensores
2018-03-15 Ajusta los valores de saturación de sensores y posición
2018-03-15 Corrige lectura de botón a logica positiva
2018-03-15 Corrige lecturas de línea a lógica positiva
2018-03-15 Añade configuración de Timer1 para cálculo de posición y PID
2018-03-15 Cambia el timer al Timer2
2018-03-16 Añade módulo de arranque para carreras; 5s para iniciar
2018-03-16 Añade control de velocidad a la función del Timer para sincronizarlo
2018-03-17 Añade configuración del Timer3 para ajustes via Serial-BT
2018-03-17 Añade control de nivel de batería
2018-03-17 Añade parada de emergencia al perder pista
2018-03-18 Añade filtro a la lectura de Batería
2018-03-18 Cambia el canal del TimerPID
2018-03-18 Añade control de encoders
2018-03-20 Añade configuración para el ESC del Brushless de succión
2018-03-21 Ajusta valores de lectura de batería
2018-03-22 Ajusta la lectura del nivel de Batería
2018-03-22 Cambia canales del TimerPID
2018-03-22 Ajusta el tiempo sin pista para parada de emergencia en competición
2018-03-22 Añade cálculo de velocidad en m/s usando encoders
2018-03-22 Añade control de velocidad de Brushless
2018-03-22 Añade lectura del MPU9250
2018-03-23 Ajusta valores de mapeo de batería
2018-03-23 Añade parada de emergencia si todos los sensores detectan línea
2018-03-23 Añade función incial de detección de curvas y rectas por encoders
2018-03-23 Añade valores PIDV para pruebas en modo competición
2018-03-23 Imprime el valor de la bateria al pulsar el botón
2018-03-24 Corrige fallo en parada de emergencia
2018-03-28 Añade gestión de cuadratura de sensores
2018-03-28 Implementa mapeo de circuito para acelerar en rectas
2018-03-29 Indenta en columna las variables globales
2018-03-29 Añade ficheros de configuración para VSCode
2018-03-29 Gestiona Brushless mediante Timer para evitar incompatibilidades con PID
2018-03-29 Añade compensaciones a los motores
2018-03-29 Elimina println innecesario
2018-03-29 Soluciona problema de conteo de ticks en cuadratura
2018-03-29 Añade funciones de pausa y reanudado de Timers
2018-03-30 Añade menú de ajustes para la cruceta de botones
2018-03-30 Configura el formateo con Clang
2018-03-30 Realiza formate completo con Clang
2018-03-31 Corrige condiciones para realizar mapeo de circuito
2018-03-31 Actualiza los ticks/mm para cuadratura
2018-03-31 Corrige mapeo de pista; reseteo de ticks
2018-04-09 Soluciona bug en saturación de sensores
2018-04-09 Añade control de distancia frontal con otros robots
2018-04-09 Aumenta valor de saturación baja para sensores de pista
2018-04-09 Actualiza gitignore
2018-04-11 Añade modo menú al pulsar abajo-derecha
2018-04-11 Documenta funciones del menú
2018-04-11 Establece las variables reales para el menú
2018-04-11 Añade configuraciones de menú de pista
2018-04-11 Mueve el calibrado de sensores a los botones izquierdo-derecho
2018-04-11 Elimina distinciones de modoCompetición
2018-04-11 Actualiza asignación de velocidades
2018-04-13 Cambia todos los `velocidadBase` por `velocidad` para config en menú
2018-04-13 Cambia el uso de las constantes del PID para configurar mediante menú
2018-04-13 Añade función de salida de menú
2018-04-24 Añade filtro para descartar lineas falsas
2018-04-24 Añade correcciones en la parada de emergencia
2018-04-24 Corrige saturación en la lectura
2018-04-24 Actualiza funciones del Menú
2018-04-25 Ajusta variables al pausar los timers
2018-05-06 Añade configuración de Saturaciones para cada modo
2018-05-06 Imprime valores de cailbración de línea
2018-05-06 Añade calibración para Degradado
2018-05-06 Añade cálculo de posición en Pista Degradados
2018-05-06 Añade funciones de debug comentadas
2018-05-16 Añade check en calibración de línea para guardar un tracking de posición
2018-05-16 Añade margen del 75% en el estado de batería
2018-05-16 Añade función simple de configuración para competición
2018-06-03 Mejora calibrado sensores en Degradado
2018-06-03 Ajusta calculo de batería y línea
2018-06-03 Actualiza cálculo de posición en Degradado
2018-06-03 Ajusta el PID para evitar oscilaciones en Degradado
2018-06-03 Ajusta el PID frontal
2018-06-03 Ajusta asignación de correcciones cuando esté el robot en movimiento
2018-06-03 Añade función de cambio de carril
2018-06-03 Añade functión de lectura digital para el multiplexador
2018-06-03 Corrige almacenado de valores raw
2018-06-03 Añade función de lectura de sensores laterales
2018-06-03 Ajusta funciones y tiempos de Timers
2018-06-03 Añade variables de control y mejora el sistema de inicio del robot
2018-06-03 Actualiza saturaciones por defecto en línea
2018-06-03 Separa en función la busqueda de línea principal
2018-06-06 Borra codigo duplicado
2018-06-06 Corrige sintaxis
2018-06-06 Corrige secuencia de inicio
2018-07-12 Actualiza cálculo de velocidad en m/s
2018-07-12 Corrige valores de medición de batería
2018-07-12 Mejora indicadores LED de batería y configuración Brushless
2018-09-28 Actualiza calibración, control de línea y varias mejoras
2018-10-05 Normaliza código estable línea
2018-10-07 Corrige menú cambiado
2018-10-07 Añade aviso de límite de PWM
2018-10-21 Soluciona calibrado y cálculo de posición
2018-10-25 Ñapea los sensores
2018-10-27 Inicia ESC en paralelo
2018-10-27 Añade nuevo menú de Velocidades y segundo arranque
2018-10-28 Elimina código no usado y mejora control de motores
2018-10-28 Actualiza pines motores DragonA
2018-11-04 Habilita de nuevo los 12 sensores del morro ancho
2018-11-04 Actualiza valores de PID en función de Dragon A o B
2018-12-21 Elimina librería Wire.c debido a problemas de congelamiento de programa
2018-12-21 Establece prioridades de Timers mediante nvic
2018-12-21 Ajusta valores del PID para variar en función del Morro
2019-01-12 Elimina saturaciones estáticas y añade definiciones
2019-01-12 Añade cáluculo de posición máxima en línea
2019-01-12 Elimina mapeo de umbrales
2019-01-12 Mapea correctamente la posición de la línea
2019-01-12 Mejora la lectura de sensores calibrados
2019-04-05 Elimina Wire definitivamente
2019-04-05 Añade soporte para uso de PWM en %
2019-04-05 Actualiza valores de velocidad y PID
2019-04-07 Pasa sensores a digital
2019-04-07 Ajusta tiempo de inicio y tipo de LiPo
2019-04-07 Ajusta las velocidades de Succión
2019-07-08 Ajustes varios y cambios en menú
2019-09-15 Añade código para control de Brushless
2019-09-15 Añade modelos 3D
2019-09-15 Añade diseño de PCBs
2019-09-15 Añade ficheros stl
2019-09-15 Añade imágenes de presentación
2019-09-15 Actualiza README
2023-03-17 Añade comprobación de calibración correcta y ajustes en manejo de brushless
2023-05-01 Actualiza README y reorganiza ficheros
